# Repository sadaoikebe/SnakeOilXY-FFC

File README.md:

# FFC mod for SnakeOil-XY 3-D printer

This is a toolhead PCB suite for SnakeOil-XY 3-D printer.
* It's a combo of a toolhead PCB and a dedicated MCU. MCU is connected to the toolhead by a ribbon cable, which makes connection simpler and also makes toolhead lighter.
* It only needs USB wire and 24V power supply connected to the MCU board.
* It has an ADXL345 accelerometer on-board.
* It has an X endstop on board, which fits SnakeOilXY toolhead dimension.
* This system is compatible only with Klipper.

## Appearance

## Toolhead

This toolhead PCB can be attached onto adxl_mount to replace the ADXL345 PCB.

It's a toolhead PCB with an ADXL345 accelerometer on-board, and it has an X endstop which fits SnakeOil-XY toolhead dimension.

### Toolhead board assembly

Tricky steps are:

* The two rows of the connectors are close, so two rows of connectors must be installed facing each other. Please be careful of the polarity of the hotend fan and the part cooling fan connector... (red arrow in the picture)
* Heater cables should be soldered. One of the heater terminals is close to the FFC connector, so unfortunately, screw terminal block (KF128 etc..) wouldn't fit. It's still able to disassemble without solder iron - loosening the bolt on the hotend will do the job. (yellow arrow in the picture)
* Bypass capacitor C2 is in the way of the stepper 4-pin connector. The bottom side of the stepper connector needs to be chamfered a little.
* It has Bltouch(servo) and Zmin(probe) connectors in order to use Z probes. Bltouch, inductive probe, or klicky probe can be used. See below diagram for connection.

### Toolhead board installation

It's designed to mount onto adxl_mount, however the X endstop switch is a bit thicker than the adxl_mount. Print and use spacer in the toolhead folder.

The back side of the stepper connector may touch the M3 bolt underneath the toolhead board. In order to avoid the unwanted contact, I recommend to cut the excess wire on the bottom and apply some capton tape to have better insulation.

## MCU Board (revision 2)

For ease of connection, this board is dedicated to this FFC configuration. The MCU board just needs to be connected to the Raspberry Pi via USB and supplied with 24V power. A 1.0mm pitch 26-pin 20624 FFC cable is used.

It only supports UART-connected smart drivers (like TMC2209) for stepper motor driver. SPI or direct connections are not supported.

FFC connector can be soldered to either the front or back side of the board. Considering cooling and wiring, it's better to place it on the back side.

This board has schottky diode on it, so 24V probe can be connected to Zmin pin without frying the MCU.

Power => Blue LED

Heater and Fan MOSFETs => Yellow LED

### C1 capacity is too small
On the rev2 MCU board, the capacitance of C1 is 10uF, which does not stabilize the hotend temperature sensor reading enough. It would be better to add a larger capacitor in parallel or add a smooth_time setting in the [extruder] section.

## Klipper configuration

It assumes multi-mcu functionality of klipper firmware.

[sample printer.cfg](klipper/sample_printer.cfg)

## BOM

* RP2040-Zero
* 26-pin 350mm (180 model) / 450mm (250 model) 20624 FFC cable
* 2x 26-pin vertical thru-hole FFC receptacle
* 2x WSF3085 (MOSFET Heater)
* 2x PL4009 (MOSFET Fan)
* Stepper driver TMC2209 or other (UART connected "smart" drivers are must)
* 2-pin DC Terminal (KF128) for 24V power supply
* TVS diode (SMAJ28A) , schottky diode (1N5819) 40V
* 2x 8-pin socket (for stepper driver)
* Jumper pins
* Capacitors, resistors
* XH2.54 sockets (3x 2pin, 2x 3pin, 1x 4pin)

## TODO

### r0.1 --> r0.2

* The Drain and Source connections of the MOSFETs of the heater were reversed --> I changed the connections.
* TVS diode are reversed --> Thankfully JLCPCB engineer fixed it. Need to rotate next time.
* The clearance between the power supply/heater terminals and other parts are not enough --> Need increase the clearance.

### r0.2 --> r0.3

* Change MCU to genuine Pico as RP2040-Zero appears to be a bit unreliable
* add wiring and pattern for MAX31865 and PT100 thermistor
* add KF301 terminal for heater
* add AUX line
* add medusa toolhead support - allow for various X endstop placement

## Heater connection

The heater is assumed to be a 24V 50W, using 4 FFC cable contacts in parallel. Approx. 500mA current flows per contact.
Resistance of the heater wire is 266mΩ round trip including four screw terminals of 24V power supply and a 600mm FFC cable - which is measured by four-terminal-pair method.
When a 24V 50W heater is used, there is a loss of about 1W including circuits, cable and contacts. (225mΩ for 53cm of lead wire, 157mΩ for 14cm of lead wire, so the loss in the circuit and FFC is 133mΩ. 266mΩ round trip. This resistance value includes the resistance of four contacts on the fixture)

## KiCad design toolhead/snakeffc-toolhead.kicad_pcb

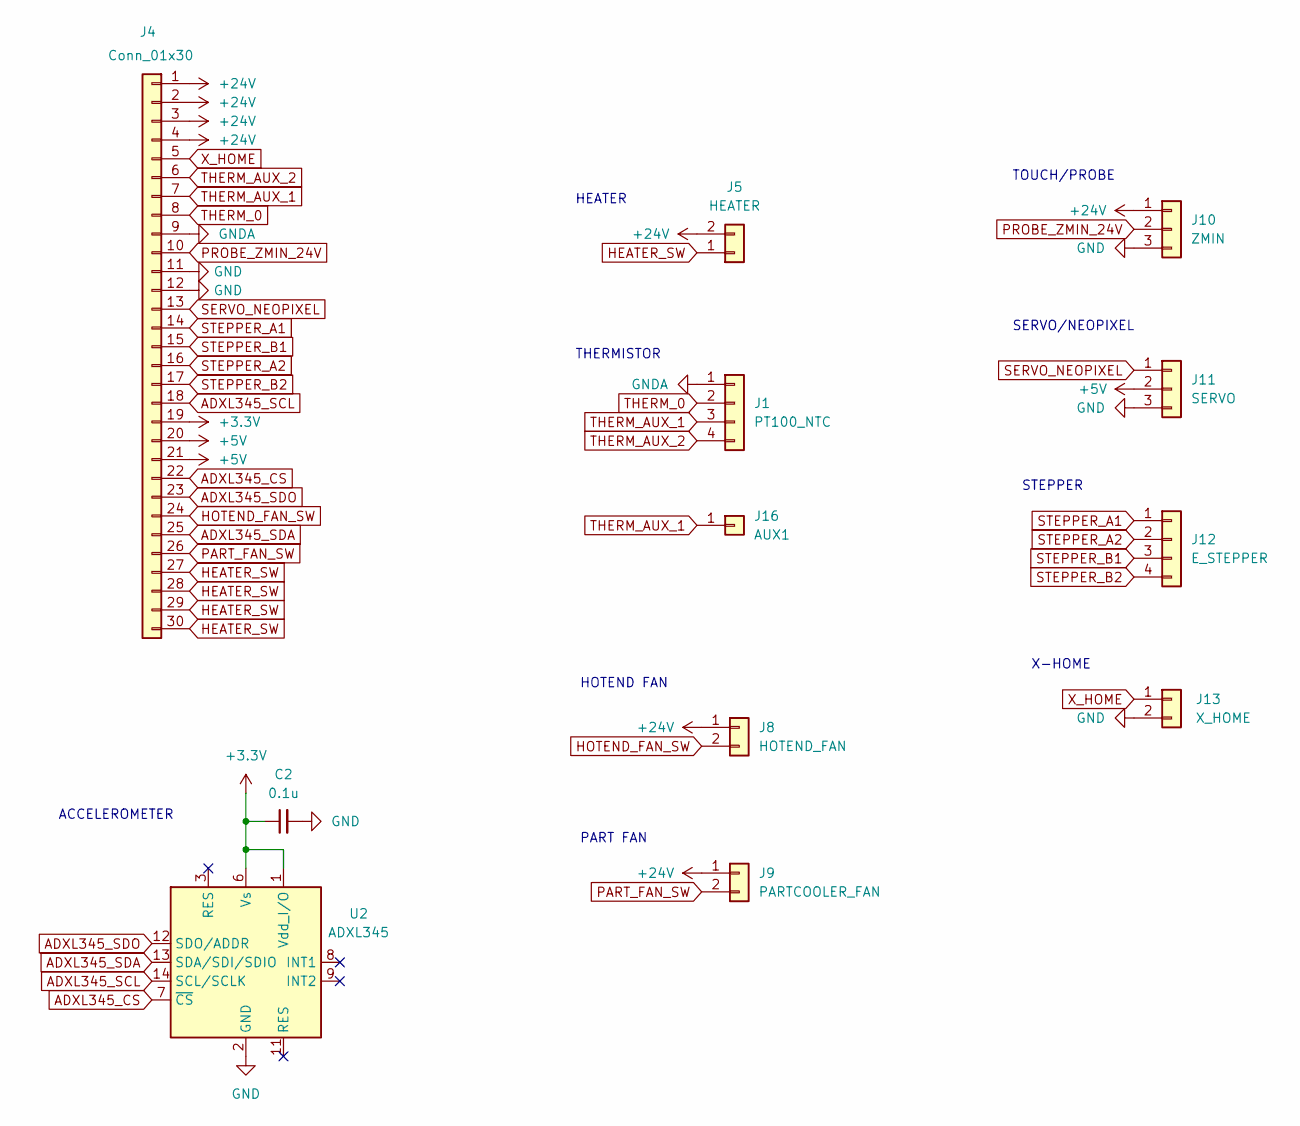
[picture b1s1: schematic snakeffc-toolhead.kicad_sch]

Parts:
C2: 0.1u; C_0603_1608Metric
J1: PT100_NTC; PinHeader_1x04_P2.54mm_Vertical
J4: Conn_01x30; ffc-30pin
J5: HEATER; KF301-5.0
J8: HOTEND_FAN; PinHeader_1x02_P2.54mm_Vertical
J9: PARTCOOLER_FAN; PinHeader_1x02_P2.54mm_Vertical
J10: ZMIN; PinHeader_1x03_P2.54mm_Vertical
J11: SERVO; PinHeader_1x03_P2.54mm_Vertical
J12: E_STEPPER; PinHeader_1x04_P2.54mm_Vertical
J13: X_HOME; limit_switch
J16: AUX1; PinHeader_1x01_P2.54mm_Vertical
U2: ADXL345; LGA-14_3x5mm_P0.8mm_LayoutBorder1x6y; LCSC C9667

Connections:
+3V3: C2.1, J4.19, U2.1 (Vdd_I/O), U2.6 (Vs)
+5V: J4.20, J4.21, J11.2
+24V: J4.1, J4.2, J4.3, J4.4, J5.2, J8.1, J9.1, J10.1
ADXL345_CS: J4.22, U2.7 (~CS)
ADXL345_SCL: J4.18, U2.14 (SCL/SCLK)
ADXL345_SDA: J4.25, U2.13 (SDA/SDI/SDIO)
ADXL345_SDO: J4.23, U2.12 (SDO/ADDR)
GND: C2.2, J4.11, J4.12, J10.3, J11.3, J13.2, U2.2 (GND), U2.4 (GND), U2.5 (GND)
GNDA: J1.1, J4.9
HEATER_SW: J4.27, J4.28, J4.29, J4.30, J5.1
HOTEND_FAN_SW: J4.24, J8.2
PART_FAN_SW: J4.26, J9.2
PROBE_ZMIN_24V: J4.10, J10.2
SERVO_NEOPIXEL: J4.13, J11.1
STEPPER_A1: J4.14, J12.1
STEPPER_A2: J4.16, J12.2
STEPPER_B1: J4.15, J12.3
STEPPER_B2: J4.17, J12.4
THERM_0: J1.2, J4.8
THERM_AUX_1: J1.3, J4.7, J16.1
THERM_AUX_2: J1.4, J4.6
X_HOME: J4.5, J13.1

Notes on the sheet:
PART FAN
HOTEND FAN
HEATER
STEPPER
X-HOME
ACCELEROMETER
THERMISTOR
SERVO/NEOPIXEL
TOUCH/PROBE

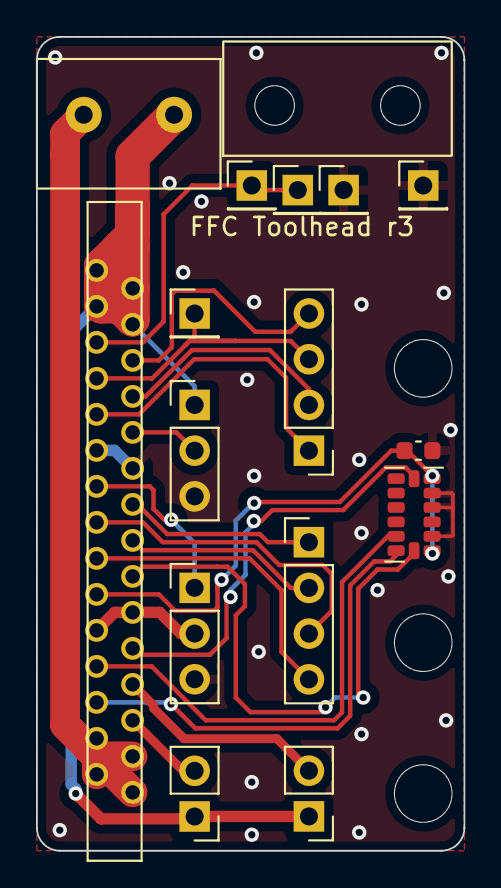
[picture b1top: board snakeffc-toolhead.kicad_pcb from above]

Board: 2 copper layers, 23.7 x 45.2 mm, 12 parts (0 on the bottom side), 22 nets.

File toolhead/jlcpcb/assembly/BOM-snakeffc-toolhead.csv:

Comment,Designator,Footprint,LCSC
0.1u,C2,C_0603_1608Metric,C14663
ADXL345,U2,LGA-14_3x5mm_P0.8mm_LayoutBorder1x6y,C9667
SERVO,J11,PinHeader_1x03_P2.54mm_Vertical,
Conn_01x30,J4,ffc-30pin,
ZMIN,J10,PinHeader_1x03_P2.54mm_Vertical,
HOTEND_FAN,J8,PinHeader_1x02_P2.54mm_Vertical,
HEATER,J5,KF301-5.0,
PARTCOOLER_FAN,J9,PinHeader_1x02_P2.54mm_Vertical,
E_STEPPER,J12,PinHeader_1x04_P2.54mm_Vertical,
X_HOME,J13,limit_switch,
AUX1,J16,PinHeader_1x01_P2.54mm_Vertical,
PT100_NTC,J1,PinHeader_1x04_P2.54mm_Vertical,

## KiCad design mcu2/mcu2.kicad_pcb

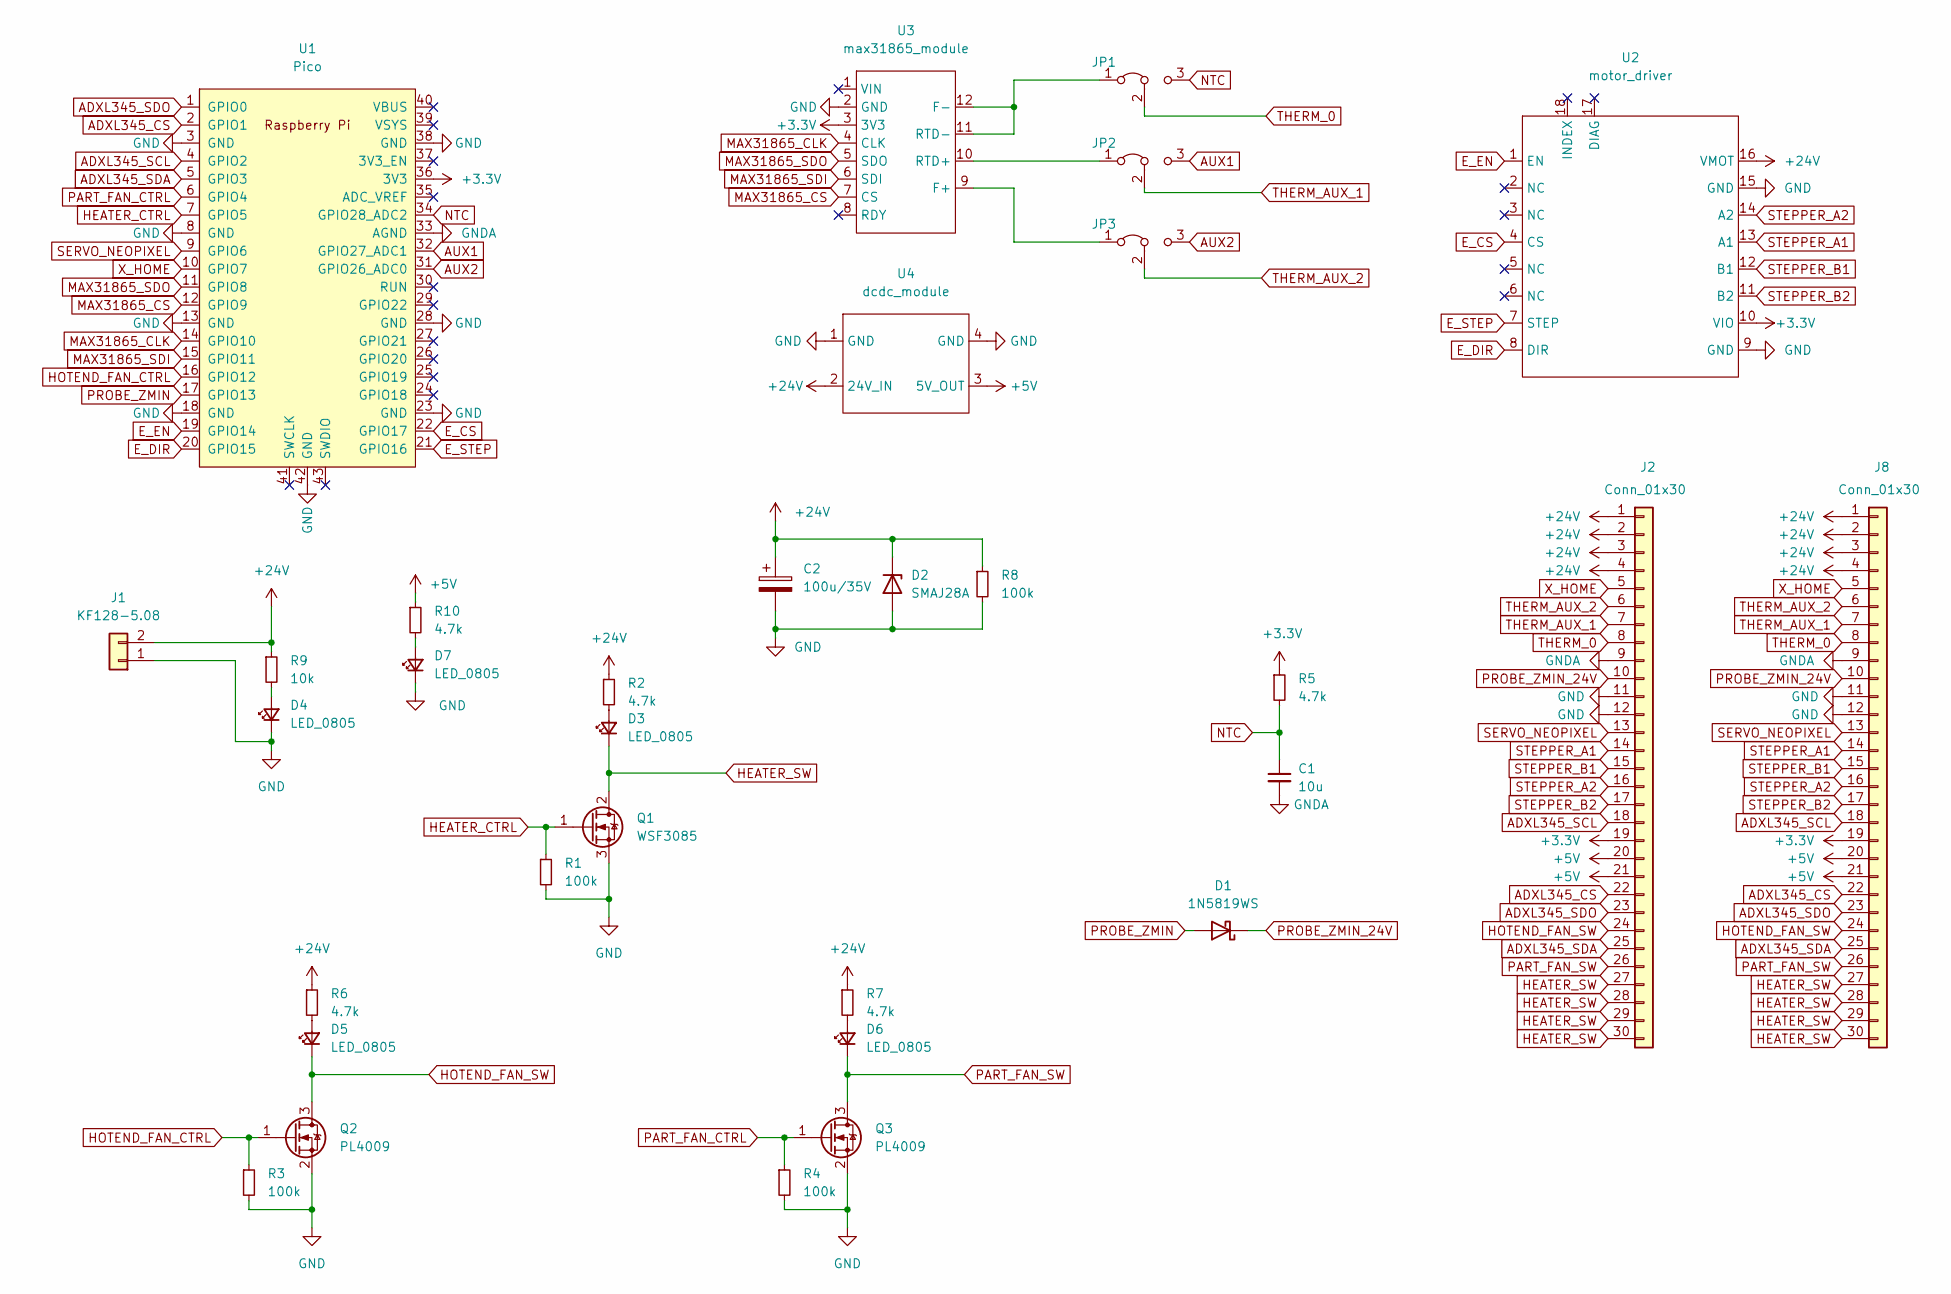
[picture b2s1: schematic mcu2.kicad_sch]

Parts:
C1: 10u; C_0805_2012Metric_Pad1.18x1.45mm_HandSolder
C2: 100u/35V; CP_Elec_6.3x7.7
D1: 1N5819WS; D_SOD-323_HandSoldering
D2: SMAJ28A; D_SMA_Handsoldering
D3, D4, D5, D6, D7: LED_0805; LED_0805_2012Metric_Pad1.15x1.40mm_HandSolder
J1: KF128-5.08
J2, J8: Conn_01x30; ffc-30pin
JP1, JP2, JP3: Jumper_3_Bridged12; SolderJumper-3_P1.3mm_Bridged12_RoundedPad1.0x1.5mm
Q1: WSF3085; TO-252-2
Q2, Q3: PL4009; SOT-23_Handsoldering
R1, R3, R4, R8: 100k; R_0805_2012Metric_Pad1.20x1.40mm_HandSolder
R2, R5, R6, R7, R10: 4.7k; R_0805_2012Metric_Pad1.20x1.40mm_HandSolder
R9: 10k; R_0805_2012Metric_Pad1.20x1.40mm_HandSolder
U1: Pico; RPi_Pico_SMD_TH
U2: motor_driver
U3: max31865_module; adafruit_max31865_module
U4: dcdc_module; dcdc_24v_5v_module

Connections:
+3V3: J2.19, J8.19, R5.1, U1.36 (3V3), U2.10 (VIO), U3.3 (3V3)
+5V: J2.20, J2.21, J8.20, J8.21, R10.1, U4.3 (5V_OUT)
+24V: C2.1, D2.1 (K), J1.2, J2.1, J2.2, J2.3, J2.4, J8.1, J8.2, J8.3, J8.4, R2.1, R6.1, R7.1, R8.1, R9.1, U2.16 (VMOT), U4.2 (24V_IN)
ADXL345_CS: J2.22, J8.22, U1.2 (GPIO1)
ADXL345_SCL: J2.18, J8.18, U1.4 (GPIO2)
ADXL345_SDA: J2.25, J8.25, U1.5 (GPIO3)
ADXL345_SDO: J2.23, J8.23, U1.1 (GPIO0)
AUX1: JP2.3 (B), U1.32 (GPIO27_ADC1)
AUX2: JP3.3 (B), U1.31 (GPIO26_ADC0)
E_CS: U1.22 (GPIO17), U2.4 (CS)
E_DIR: U1.20 (GPIO15), U2.8 (DIR)
E_EN: U1.19 (GPIO14), U2.1 (EN)
E_STEP: U1.21 (GPIO16), U2.7 (STEP)
GND: C2.2, D2.2 (A), D4.1 (K), D7.1 (K), J1.1, J2.11, J2.12, J8.11, J8.12, Q1.3 (S), Q2.2 (S), Q3.2 (S), R1.2, R3.2, R4.2, R8.2, U1.3 (GND), U1.8 (GND), U1.13 (GND), U1.18 (GND), U1.23 (GND), U1.28 (GND), U1.38 (GND), U1.42 (GND), U2.9 (GND), U2.15 (GND), U3.2 (GND), U4.1 (GND), U4.4 (GND)
GNDA: C1.2, J2.9, J8.9, U1.33 (AGND)
HEATER_CTRL: Q1.1 (G), R1.1, U1.7 (GPIO5)
HEATER_SW: D3.1 (K), J2.27, J2.28, J2.29, J2.30, J8.27, J8.28, J8.29, J8.30, Q1.2 (D)
HOTEND_FAN_CTRL: Q2.1 (G), R3.1, U1.16 (GPIO12)
HOTEND_FAN_SW: D5.1 (K), J2.24, J8.24, Q2.3 (D)
MAX31865_CLK: U1.14 (GPIO10), U3.4 (CLK)
MAX31865_CS: U1.12 (GPIO9), U3.7 (CS)
MAX31865_SDI: U1.15 (GPIO11), U3.6 (SDI)
MAX31865_SDO: U1.11 (GPIO8), U3.5 (SDO)
NTC: C1.1, JP1.3 (B), R5.2, U1.34 (GPIO28_ADC2)
unnamed: D3.2 (A), R2.2
unnamed: D4.2 (A), R9.2
unnamed: D5.2 (A), R6.2
unnamed: D6.2 (A), R7.2
unnamed: D7.2 (A), R10.2
unnamed: JP1.1 (A), U3.11 (RTD-), U3.12 (F-)
unnamed: JP2.1 (A), U3.10 (RTD+)
unnamed: JP3.1 (A), U3.9 (F+)
PART_FAN_CTRL: Q3.1 (G), R4.1, U1.6 (GPIO4)
PART_FAN_SW: D6.1 (K), J2.26, J8.26, Q3.3 (D)
PROBE_ZMIN: D1.2 (A), U1.17 (GPIO13)
PROBE_ZMIN_24V: D1.1 (K), J2.10, J8.10
SERVO_NEOPIXEL: J2.13, J8.13, U1.9 (GPIO6)
STEPPER_A1: J2.14, J8.14, U2.13 (A1)
STEPPER_A2: J2.16, J8.16, U2.14 (A2)
STEPPER_B1: J2.15, J8.15, U2.12 (B1)
STEPPER_B2: J2.17, J8.17, U2.11 (B2)
THERM_0: J2.8, J8.8, JP1.2 (C)
THERM_AUX_1: J2.7, J8.7, JP2.2 (C)
THERM_AUX_2: J2.6, J8.6, JP3.2 (C)
X_HOME: J2.5, J8.5, U1.10 (GPIO7)

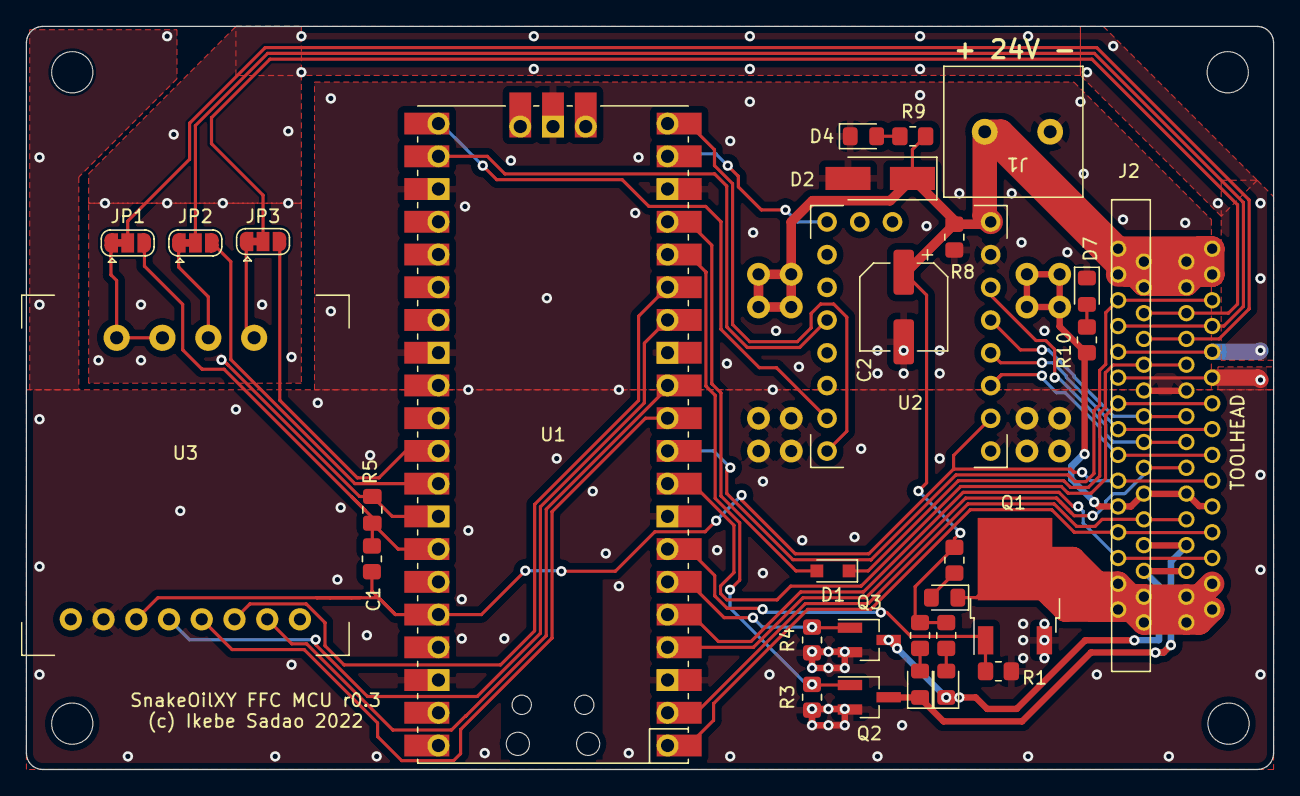
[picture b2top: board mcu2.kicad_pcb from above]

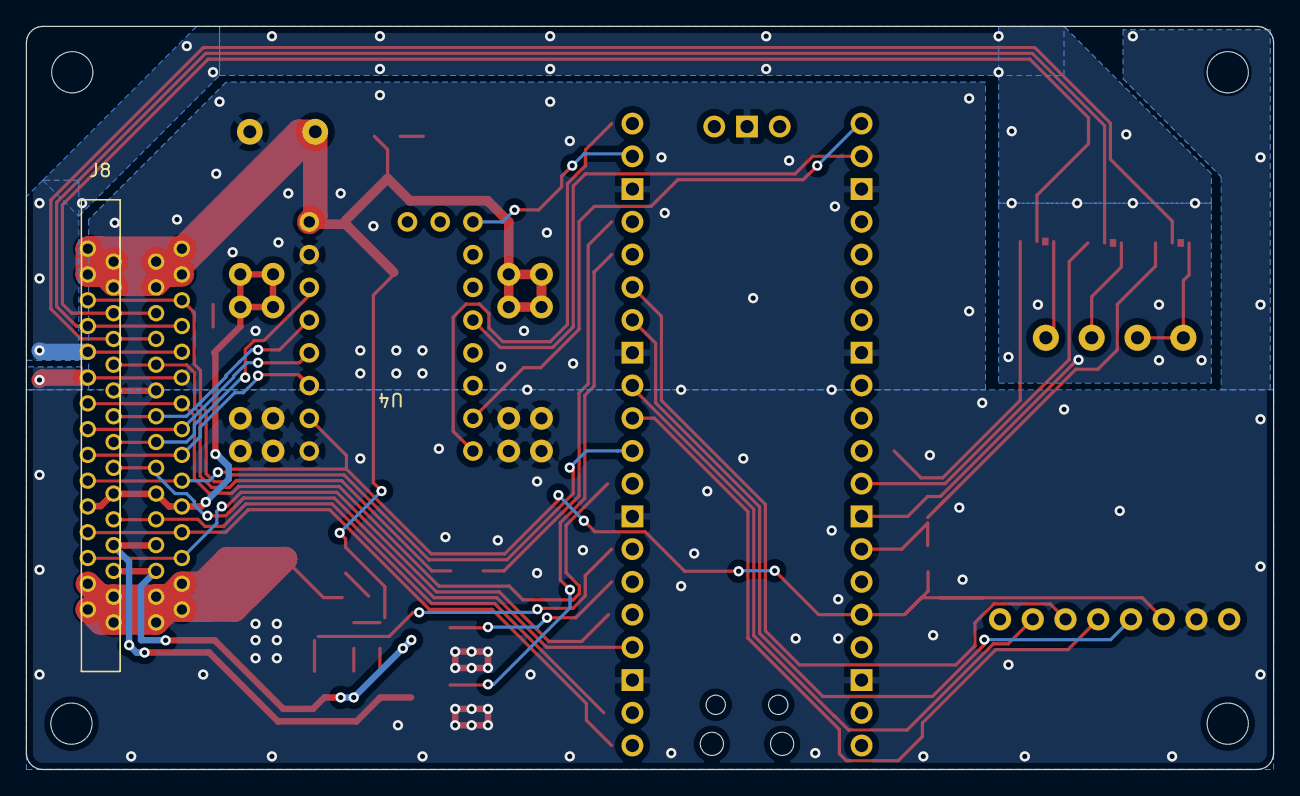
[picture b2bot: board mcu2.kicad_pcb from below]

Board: 2 copper layers, 96.8 x 57.7 mm, 32 parts (2 on the bottom side), 45 nets.

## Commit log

2022-02-07 gnd plane increased
2022-02-07 jlcpcb ordered
2022-02-07 sample config
2022-02-08 added stepper controller on the mcu
2022-02-08 add fab info
2022-02-08 adjust hole position
2022-02-08 adjust holes and silkscreen
2022-02-08 fixed broken parts
2022-02-08 smd schottky and jumper, ordered JLCPCB
2022-02-09 24V connector position adjusted - ordered again
2022-03-01 change footprint on heater mos
2022-03-01 add description
2022-03-01 change images
2022-03-01 add image
2022-03-01 add diagram
2022-03-03 add picture
2022-03-04 added sample printer.cfg, removed old mcu
2022-03-04 update description
2022-03-04 correct orientation for TVS diode
2022-03-04 add voron mod
2022-03-06 r2 jlcpcb
2022-03-07 add a FFC connector on back side
2022-03-07 change description wording
2022-03-18 mounter v2
2022-03-18 make room for panels
2022-03-22 description updated
2022-03-22 description updated 2
2022-03-22 add toolhead installation
2022-03-22 added diagram
2022-03-23 revise description
2022-03-23 revise description further
2022-03-25 sensor reading
2022-07-25 clockwork2 rc
2022-08-08 r0.3 todo list
2022-09-11 Create LICENSE
2022-09-27 mcu schematic r3
2022-09-27 toolhead r3 schematic
2022-09-27 add footprints
2022-09-27 remove unnecessary footprints
2022-09-28 mcu2 wiring
2022-09-28 mcu2 gerber
2022-09-28 change hole size
2022-09-28 toolhead artwork
2022-10-06 r3 jlcpcb
